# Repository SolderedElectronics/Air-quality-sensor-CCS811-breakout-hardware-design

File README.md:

# Air quality sensor CCS811 breakout Hardware design

## About the product

|  |
| :----------------------------------------------------------: |
|      [Buy Air quality sensor CCS811 breakout](https://www.solde.red/333009)      |

The CCS811 sensor is designed to measure various volatile particles in the air (TVOC - Total Volatile Organic Compounds), which include eCO2 (CO2 equivalent) and MOX (metal oxides). VOCs are generally defined as air pollutants, and can come from a variety of sources, starting with ordinary breathing, smoking, coloring, welding, and generally all processes that release particles into the surrounding air.

This sensor is often used to measure indoor air quality, which can work very well and indicate current air pollution, for example, in an office. It communicates via I2C, making it easy to connect, especially through easyC. Sensor itself should be powered for at least 20 minutes to start making accurate readings.

## Repository contents

All Soldered Electronics hardware designed in KiCAD, and repositories are organized in the following way:

- CAD folder - contains KiCAD files (Schematics, Board, Panel Board), sorted by version. Change log lists all changes between versions.
- OUTPUTS - contains useful files, such as Bill of Materials (BOM), PDF of schematics, 3D .step file of the board and gerber files, sorted by version. 
- OUTPUTS -> Compliance - Certificates and useful legal stuff. 

## Want to contribute?

Please feel free to submit a pull request if you have any contributions. We encourage you to submit an issue or pull request if you find a bug. 

## About Soldered

At Soldered, we design and manufacture a wide selection of electronic products to help you turn your ideas into acts and bring you one step closer to your final project. Our products are intented for makers and crafted in-house by our experienced team in Osijek, Croatia. We believe that sharing is a crucial element for improvement and innovation, and we work hard to stay connected with all our makers regardless of their skill or experience level. Therefore, all our products are open-source. Finally, we always have your back. If you face any problem concerning either your shopping experience or your electronics project, our team will help you deal with it, offering efficient customer service and cost-free technical support anytime. Some of those might be useful for you:

- [Web Store](https://www.soldered.com/shop)
- [Tutorials & Projects](https://soldered.com/learn)
- [Community & Technical support](https://soldered.com/community)

## License info

All Soldered open-source hardware (OSH) is under The TAPR Open Hardware License. Read more in the LICENSE file. 

No warranty - all designs in this repository are distributed in the hope that they will be useful, but without any warranty. They are provided "AS IS", therefore without warranty of any kind, either expressed or implied. The entire quality and performance of what you do with the contents of this repository are your responsibility. In no event, Soldered Electronics will be liable for your damages, losses, including any general, special, incidental or consequential damage arising out of the use or inability to use the contents of this repository. 

## Have fun! 
And thank you from your fellow makers at Soldered Electronics.

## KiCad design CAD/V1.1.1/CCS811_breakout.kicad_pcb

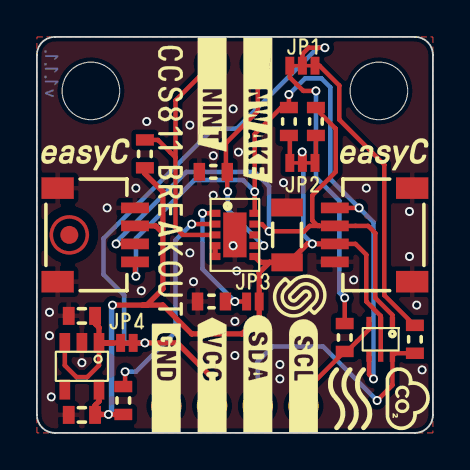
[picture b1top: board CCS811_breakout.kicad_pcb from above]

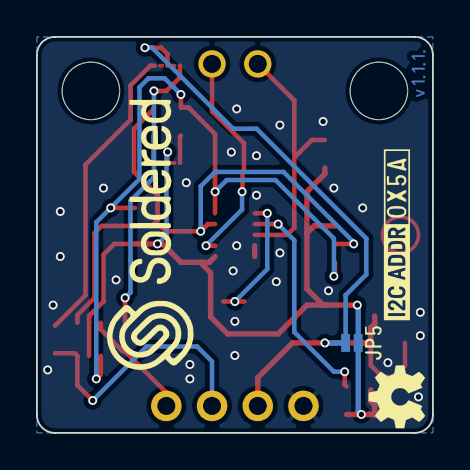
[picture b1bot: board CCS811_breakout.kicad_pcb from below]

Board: 2 copper layers, 22.0 x 22.0 mm, 26 parts (3 on the bottom side), 17 nets.

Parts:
C1: 10uF; 1206C
C2, C3: 2.2uF; 0603C
FD1: FIDUCIAL; FIDUCIAL_23
H1, H2: HOLE_3.2mm
JP1, JP2: SMD_JUMPER_3_PAD_TRACE
JP3, JP5: SMD_JUMPER
JP4: SMD-JUMPER-CONNECTED_TRACE_SLODERMASK
K1: HEADER_MALE_2X1
K2: HEADER_MALE_4X1
K3, K4: easyC-SMD; easyC-connector
R1, R2, R5, R6: 4.7k; 0603R
R3, R4, R7, R8: 10k; 0603R
U1: NMOS-DUAL; SOT-363
U2: CCS811B-JOPR; CCS811
U3: SE5218; SOT-23-5

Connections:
3V3: C1.2, C3.2, JP2.2, JP3.2, JP5.2, K3.3 (3V3), K4.3 (3V3), R1.2, R2.2, U1.2 (G2), U1.5 (G1), U2.6 (VDD), U3.5 (VOUT)
5V: JP1.2, JP4.2, JP5.1, K2.2
GND: C1.1, C2.1, C3.1, K2.1, K3.4 (GND), K3.5 (SHIELD), K4.4 (GND), K4.5 (SHIELD), R5.1, R6.1, U2.11 (GND), U3.2 (GND)
NINT: K1.1, R1.1, U2.3 (nINT)
NWAKE: K1.2, R6.2, U2.7 (nWAKE)
unnamed: C2.2, JP4.1, U3.1 (VIN), U3.3 (EN)
unnamed: JP3.1, R5.2, U2.1 (ADD)
unnamed: R2.1, U2.2 (nRESET)
unnamed: U2.4 (PWM), U2.5 (SENSE)
SCL3,3: K3.1 (SCL), K4.1 (SCL), R8.1, U1.4 (S1), U2.10 (SCL)
SCL5: K2.4, R4.2, U1.3 (D1)
SCL_PULL3,3: JP2.1, R8.2
SCL_PULL5: JP1.1, R4.1
SDA3,3: K3.2 (SDA), K4.2 (SDA), R3.2, U1.1 (S2), U2.9 (SDA)
SDA5: K2.3, R7.1, U1.6 (D2)
SDA_PULL3,3: JP2.3, R3.1
SDA_PULL5: JP1.3, R7.2

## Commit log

2022-08-06 Updating open source files.
